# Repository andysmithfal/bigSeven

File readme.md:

bigSeven
========

An Open Source Hardware project for making BIG seven segment displays. 

A simple design based on a 595 shift register and some beefy power transistors, and is designed to chain together.

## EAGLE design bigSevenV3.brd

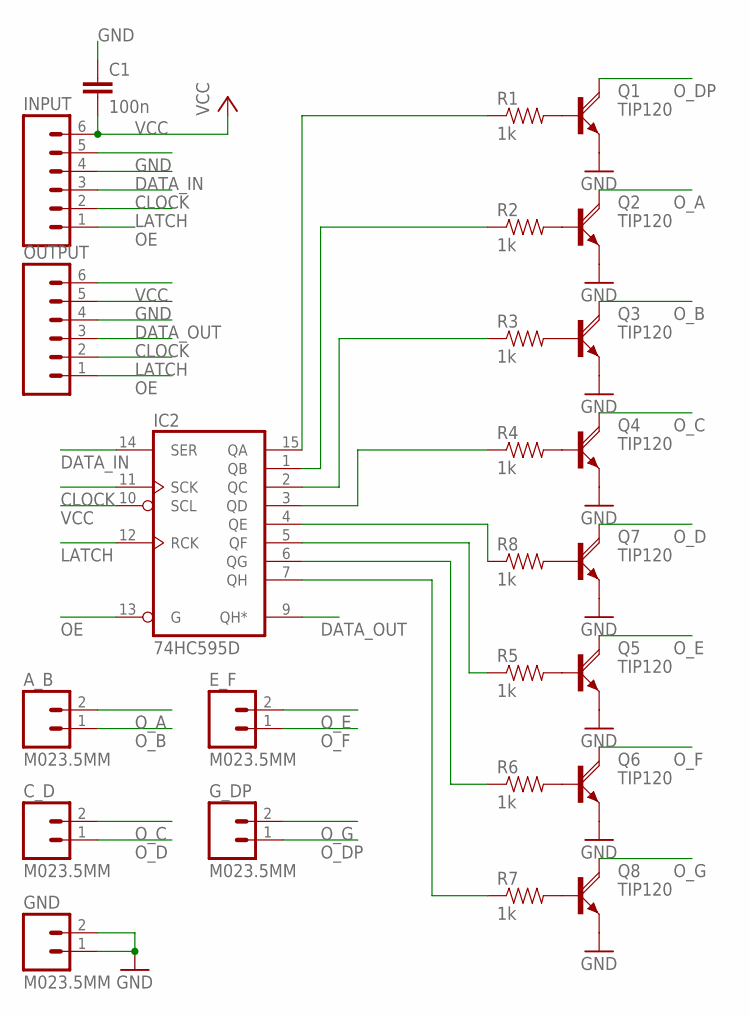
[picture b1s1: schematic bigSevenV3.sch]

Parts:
A_B: M023.5MM; SCREWTERMINAL-3.5MM-2
C1: 100n; 0805
C_D: M023.5MM; SCREWTERMINAL-3.5MM-2
E_F: M023.5MM; SCREWTERMINAL-3.5MM-2
GND: M023.5MM; SCREWTERMINAL-3.5MM-2
G_DP: M023.5MM; SCREWTERMINAL-3.5MM-2
IC2: 74HC595D; SO16
INPUT: M06LOCK; 1X06_LOCK
OUTPUT: M06LOCK; 1X06_LOCK
Q1, Q2, Q3, Q4, Q5, Q6, Q7, Q8: TIP120; TO220AH
R1, R2, R3, R4, R5, R6, R7, R8: 1k; 0805

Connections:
CLOCK: IC2.11 (SCK), INPUT.3, OUTPUT.3
DATA_IN: IC2.14 (SER), INPUT.4
DATA_OUT: IC2.9 (QH*), OUTPUT.4
GND: C1.1, GND.1, GND.2, IC2.8 (GND), INPUT.5, OUTPUT.5, Q1.E, Q2.E, Q3.E, Q4.E, Q5.E, Q6.E, Q7.E, Q8.E
LATCH: IC2.12 (RCK), INPUT.2, OUTPUT.2
unnamed: Q1.B, R1.2
unnamed: Q2.B, R2.2
unnamed: Q3.B, R3.2
unnamed: Q4.B, R4.2
unnamed: Q5.B, R5.2
unnamed: Q6.B, R6.2
unnamed: Q8.B, R7.2
unnamed: Q7.B, R8.2
unnamed: IC2.15 (QA), R1.1
unnamed: IC2.1 (QB), R2.1
unnamed: IC2.2 (QC), R3.1
unnamed: IC2.3 (QD), R4.1
unnamed: IC2.4 (QE), R8.1
unnamed: IC2.5 (QF), R5.1
unnamed: IC2.6 (QG), R6.1
unnamed: IC2.7 (QH), R7.1
OE: IC2.13 (G), INPUT.1, OUTPUT.1
O_A: A_B.2, Q2.C
O_B: A_B.1, Q3.C
O_C: C_D.2, Q4.C
O_D: C_D.1, Q7.C
O_DP: G_DP.1, Q1.C
O_E: E_F.2, Q5.C
O_F: E_F.1, Q6.C
O_G: G_DP.2, Q8.C
VCC: C1.2, IC2.10 (SCL), IC2.16 (VCC), INPUT.6, OUTPUT.6

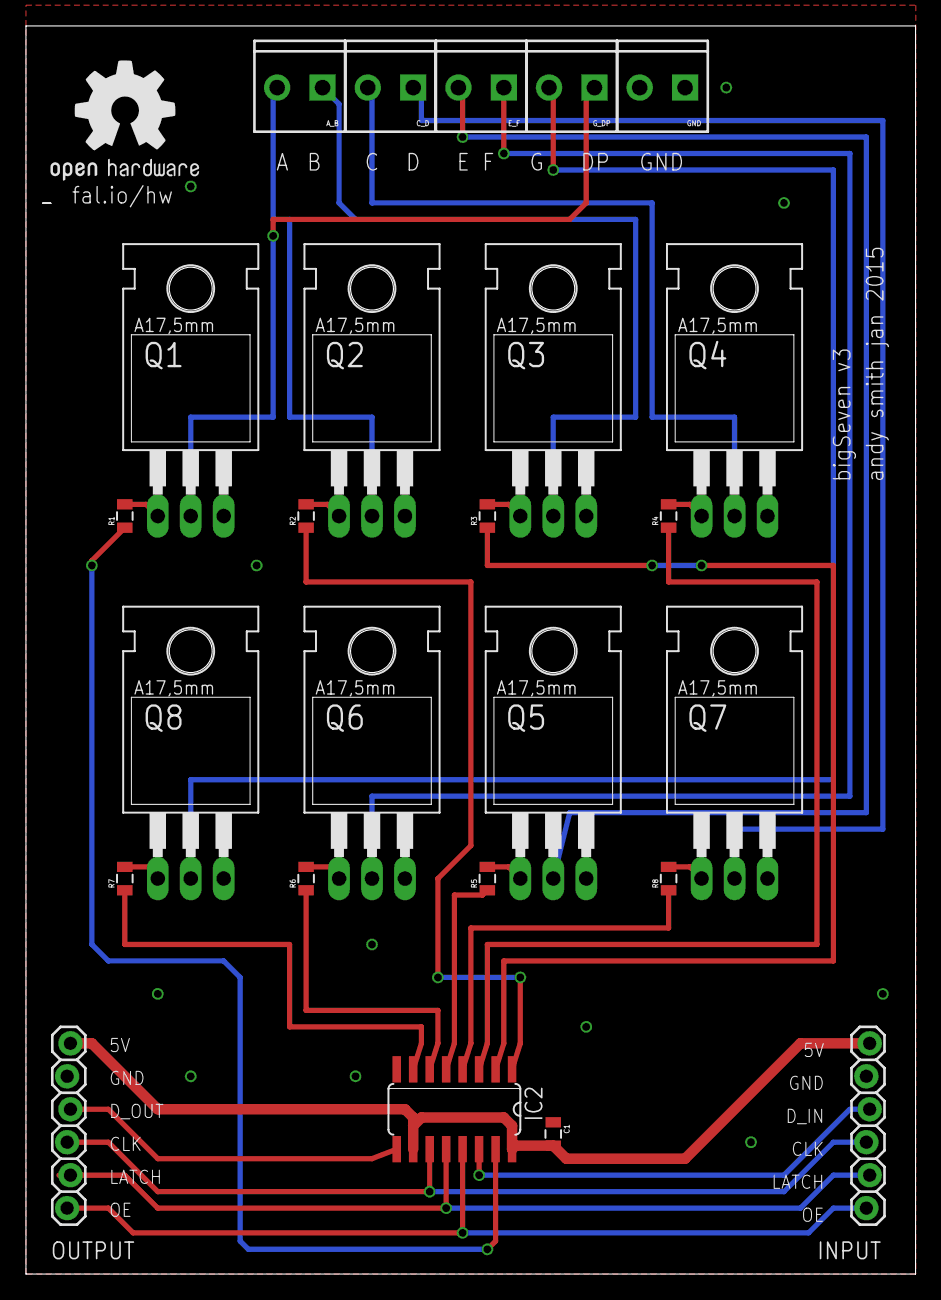
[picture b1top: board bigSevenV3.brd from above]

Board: 2 copper layers, 68.6 x 96.2 mm, 27 parts (1 on the bottom side), 31 nets.

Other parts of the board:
U$1: OSHW1
U$2: CORNWALL_25MM

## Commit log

2015-01-24 picture of displays
2015-01-24 board
2015-02-10 Board revision, changed layout for easier assembly

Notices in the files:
parts and their libraries:
SparkFun-Capacitors: Licensing: Creative Commons ShareAlike 4.0 International - https://creativecommons.org/licenses/by-sa/4.0
